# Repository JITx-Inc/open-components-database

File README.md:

# Open Component Database
 
This is an open database of components and circuit generators for automated circuit board design. Think of it as a software library for electrical engineering. We welcome contributions of component models, as well as parametric circuit generators. If you contribute to this library your expert hardware engineering knowledge becomes reusable and sharable, having the same impact as open-source software.

Components are modeled with the standardized open-source Electronic Systems Intermediate Representation (ESIR) developed by JITX for the national Electronic Resurgence Initiative.

# Organization
| File/Folder   | Description |
| ------------- |-------------|
| `artwork/`      | Examples demonstrating how to add artwork to the design. |
| `components/`      | Component data for electrical components, including circuits specific to a component. |
| `components/<manufacturer>`   | Components are organized into folders based on manufacturer |
| `components/manufacturer/<MPN>.stanza`   | There is one file per component family in the manufacturer folder (e.g. `analog-devices/ADM7150.stanza` models the ADM7150 LDOs). This file contains component data, and component-specific package models and modules.|
| `derating/`      | Contains collections of derating parameters for reliability testing. |
| `derating/space-derating.stanza`      | Derating parameters for spaceflight applications. |
| `designs/`      | Collection of example designs. [More documentation here.](designs/example-designs.md) |
| `doc/`      | Documentation. |
| `manufacturers/`      | Directory of PCB fabrication and manufacturing data like rules and stack-up definitions.|
| `modules/`      | Contains generators for subcircuits. (e.g. passive-circuits.stanza contains generators for circuits like passive filters and voltage dividers) |
| `modules/solvers`      | Contains JITX circuit solvers. (e.g. voltage-divider.stanza contains a solver for creating a resistive voltage divider taking into account component tolerance and availability) |
| `utils/`      | Utilities for modeling components and creating circuit generators|
| `utils/bundles.stanza`      | Definitions for commonly used bundles (e.g. `SPI`) |
| `utils/checks.stanza`      | Checks to run on designs (e.g. `check resistor()`|
| `utils/connects.stanza`      | Connection statements for creating io-translation/conditioning circuitry. (e.g. `isolate()`|
| `utils/generator-utils.stanza`      | General purpose utilities for modeling components and creating circuit generators. |
| `utils/generic-components.stanza`      | Collection of generic components (e.g. generic resistors, or banana-plugs)|
| `utils/landpatterns.stanza`      | Generators for land-pattern geometry (e.g. `make-qfn-landpattern()`)|
| `utils/property-structs.stanza`      | Pre-defined properties that can be applied to components, nets, modules in a design which are helpful to enable checks on the design. |
| `utils/symbols.stanza`      | Pre-defined schematic symbols (e.g. `power symbols, resistors, capacitors, diodes, etc`)|
| `utils/tolerance.stanza`      | Description of `Toleranced()` data-type and associated support functions. |

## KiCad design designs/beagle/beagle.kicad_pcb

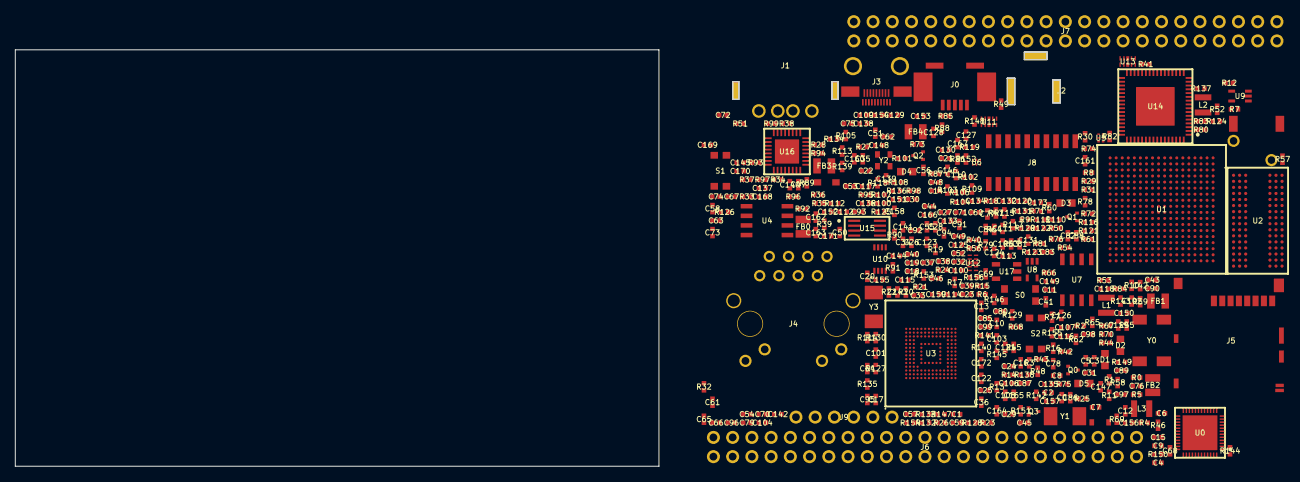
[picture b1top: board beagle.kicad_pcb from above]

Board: 4 copper layers, 383 parts (0 on the bottom side), 308 nets, no tracks yet.

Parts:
C0, C1, C2, C3, C4, C5, C6, C7, C8, C9, C10, C11, C12, C13, C14, C15, C16, C17, C18, C19, C20, C21, C22, C23, C24, C25, C26, C27, C28, C29, C30, C31, C32, C33, C34, C35, C36, C37, C38, C39, C40, C41, C42, C43, C44, C45, C46, C47, C48, C49, C50, C51, C52, C53, C54, C55, C56, C57, C58, C59, C60, C61, C62, C63, C64, C65, C66, C67, C68, C69, C70, C71, C72, C73, C74, C75, C76, C77, C78, C79, C80, C81, C82, C83, C84, C85, C86, C87, C88, C89, C90, C91, C92, C93, C94, C95, C96, C97, C98, C99, C100, C101, C102, C103, C104, C105, C106, C107, C108, C109, C110, C111, C112, C113, C114, C115, C116, C117, C118, C119, C120, C121, C122, C123, C124, C125, C126, C127, C128, C129, C130, C131, C132, C133, C134, C135, C136, C137, C138, C139, C140, C141, C142, C143, C144, C145, C146, C147, C148, C149, C150, C151, C152, C153, C154, C155, C156, C157, C158, C159, C160, C161, C162, C163, C164, C165, C166, C167, C168, C169, C170, C171, C172, C173: ipc-two-pin-package$83
D1, D2, D3, D4, D5: ipc-two-pin-package$360
FB0, FB1, FB2, FB3, FB4: ipc-two-pin-package$214
J0: usb_5Ffootprint
J1: usb-87520-0010BLF-package
J2: footprint$55
J3: hdmi-10118241-001RLF-package
J4: eth_5Ffootprint
J5: usd-2201778-1-package
J6, J7: p46_5Ffootprint
J8: RSM-110-02-S-D_5Ffootprint
J9: _5F68000-406HLF_5Ffootprint
L1, L2, L3: ind_5Ffootprint
Q0, Q1, Q2, Q3: SOT-523
R0, R1, R2, R3, R4, R5, R6, R7, R8, R9, R10, R11, R12, R13, R14, R15, R16, R17, R18, R19, R20, R21, R22, R23, R24, R25, R26, R27, R28, R29, R30, R31, R32, R33, R34, R35, R36, R37, R38, R39, R40, R41, R42, R43, R44, R45, R46, R47, R48, R49, R50, R51, R52, R53, R54, R55, R56, R57, R58, R59, R60, R61, R62, R63, R64, R65, R66, R67, R68, R69, R70, R71, R72, R73, R74, R75, R76, R77, R78, R79, R80, R81, R82, R83, R84, R85, R86, R87, R88, R89, R90, R91, R92, R93, R94, R95, R96, R97, R98, R99, R100, R101, R102, R103, R104, R105, R106, R107, R108, R109, R110, R111, R112, R113, R114, R115, R116, R117, R118, R119, R120, R121, R122, R123, R124, R125, R126, R127, R128, R129, R130, R131, R132, R133, R134, R135, R136, R137, R138, R139, R140, R141, R142, R143, R144, R145, R146, R147, R148, R149, R150, R151, R152, R153, R154, R155, R156: ipc-two-pin-package$83
S0, S1, S2: footprint$17
U0: qfn-package$76
U1: bga-pkg$130
U2: bga-pkg$301
U3: bga-pkg$326
U4: footprint$12
U5, U6: uson-dry0006a
U7: footprint$42
U8, U9: dck-R-PDSO-G5
U10: dcu-S-PDSO-G8
U11, U12: footprint$61
U13: footprint$67
U14: QFN64_5FWITHTHERMALPAD
U15: sm8-package$425
U16: QFN32_5FWITHTHERMALPAD
U17: SOT-23-5-package
Y0: xtal_5Ffootprint
Y1, Y3: SMD-2$370
Y2: SDMB-24-576MHZ-package

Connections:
AIN0: J7.39, U1.B6
AIN1: J7.40, U1.C7
AIN2: J7.37, U1.B7
AIN3: J7.38, U1.A7
AIN4: J7.33, U1.C8
AIN5: J7.36, U1.B8
AIN6: J7.35, U1.A8
AIN7: R77.2, R78.2, U1.C9
B_UART0_RX: J9.4, R114.2, U10.2
B_UART0_TX: J9.5, U10.3
CLKOUT2: J7.41, J8.18, R120.2, R121.2
CLKOUT_SRC: R120.1, U1.D14
CPU_vdd_pll: C47.1, C48.1, C49.1, C50.1, FB0.2, U1.E7, U1.H15, U1.R10, U1.R11
DDR3L_ZQ: R12.1, U2.L8
DDR_A0: U1.F3, U2.N3
DDR_A1: U1.H1, U2.P7
DDR_A2: U1.E4, U2.P3
DDR_A3: U1.C3, U2.N2
DDR_A4: U1.C2, U2.P8
DDR_A5: U1.B1, U2.P2
DDR_A6: U1.D5, U2.R8
DDR_A7: U1.E2, U2.R2
DDR_A8: U1.D4, U2.T8
DDR_A9: U1.C1, U2.R3
DDR_A10: U1.F4, U2.L7
DDR_A11: U1.F2, U2.R7
DDR_A12: U1.E3, U2.N7
DDR_A13: U1.H3, U2.T3
DDR_A14: U1.H4, U2.T7
DDR_BA0: U1.C4, U2.M2
DDR_BA1: U1.E1, U2.N8
DDR_BA2: U1.B3, U2.M3
DDR_CASn: U1.F1, U2.K3
DDR_CKE: R7.1, U1.G3, U2.K9
DDR_CLK: U1.D2, U2.J7
DDR_CLKn: U1.D1, U2.K7
DDR_CSn: U1.H2, U2.L2
DDR_D0: U1.M3, U2.E3
DDR_D1: U1.M4, U2.F7
DDR_D2: U1.N1, U2.F2
DDR_D3: U1.N2, U2.F8
DDR_D4: U1.N3, U2.H3
DDR_D5: U1.N4, U2.H8
DDR_D6: U1.P3, U2.G2
DDR_D7: U1.P4, U2.H7
DDR_D8: U1.J1, U2.D7
DDR_D9: U1.K1, U2.C3
DDR_D10: U1.K2, U2.C8
DDR_D11: U1.K3, U2.C2
DDR_D12: U1.K4, U2.A7
DDR_D13: U1.L3, U2.A2
DDR_D14: U1.L4, U2.B8
DDR_D15: U1.M1, U2.A3
DDR_DQM0: U1.M2, U2.E7
DDR_DQM1: U1.J2, U2.D3
DDR_DQS0: U1.P1, U2.F3
DDR_DQS1: U1.L1, U2.C7
DDR_DQSN0: U1.P2, U2.G3
DDR_DQSN1: U1.L2, U2.B7
DDR_ODT: U1.G1, U2.K1
DDR_RASn: U1.G4, U2.J3
DDR_RESETn: R6.1, U1.G2, U2.T2
DDR_VREF: C60.1, C107.1, C108.1, R13.2, R14.1, U1.J4, U2.H1, U2.M8
DDR_WEn: U1.B2, U2.L3
DGND: C0.2, C1.2, C2.2, C3.2, C4.2, C5.2, C6.2, C7.2, C8.2, C9.2, C10.2, C11.2, C12.2, C13.2, C14.2, C15.2, C16.2, C17.2, C18.2, C19.2, C20.2, C21.2, C22.2, C23.2, C24.2, C25.2, C26.2, C27.2, C28.2, C29.2, C30.2, C31.2, C32.2, C33.2, C34.2, C35.2, C36.2, C37.2, C38.2, C39.2, C40.2, C41.2, C42.2, C43.2, C44.2, C45.2, C46.2, C47.2, C48.2, C49.2, C50.2, C51.2, C52.2, C53.2, C54.2, C55.2, C56.2, C57.2, C58.2, C59.2, C60.2, C61.2, C62.2, C63.2, C64.2, C65.2, C66.2, C67.2, C68.2, C69.2, C70.2, C71.2, C72.2, C73.2, C74.2, C75.2, C76.2, C77.2, C78.2, C79.2, C80.2, C81.2, C82.2, C83.2, C84.2, C89.2, C90.2, C91.2, C92.2, C93.2, C94.2, C95.2, C96.2, C97.2, C98.2, C99.2, C100.2, C101.2, C102.2, C103.2, C104.2, C105.2, C106.2, C107.2, C108.2, C109.2, C110.2, C111.2, C112.2, C113.2, C114.2, C115.2, C116.2, C117.2, C122.2, C123.2, C125.2, C126.2, C127.2, C128.2, C129.2, C130.2, C131.2, C132.2, C133.2, C134.2, C135.2, C136.2, C137.2, C138.2, C139.2, C140.2, C141.2, C142.2, C145.2, C146.2, C147.2, C148.2, C149.2, C152.2, C153.2, C154.2, C155.2, C156.2, C157.2, C158.2, C159.2, C160.2, C161.2, C162.2, C163.2, C164.2, C165.2, C166.2, C167.2, C168.2, C169.2, C170.2, C171.2, C172.1, C173.1, FB2.1, J0.5, J1.4, J2.2, J2.3, J3.4, J3.7, J3.10, J3.13, J3.16, J4.8, J5.6, J5.10, J6.1, J6.2, J7.1, J7.2, J7.43, J7.44, J7.45, J7.46, J8.4, J8.8, J8.10, J8.12, J8.16, J8.20, J9.1, Q0.3, Q1.3, Q2.3, Q3.3, R4.2, R5.2, R7.2, R8.2, R10.2, R12.2, R14.2, R28.2, R30.2, R31.2, R32.2, R33.2, R34.2, R39.2, R41.2, R44.2, R53.2, R55.2, R65.2, R70.2, R72.2, R74.2, R76.2, R78.1, R92.2, R93.2, R94.2, R95.2, R99.2, R114.1, R116.1, R124.2, R126.2, R128.2, R130.2, R132.2, R134.2, R136.2, R138.2, R140.2, R142.2, R144.2, R146.2, R148.2, R150.2, R152.2, R154.2, S0.2, S0.4, S1.2, S1.4, S2.2, S2.4, U0.30, U0.41, U0.49, U1.A1, U1.A18, U1.F8, U1.G8, U1.G9, U1.G11, U1.G12, U1.H6, U1.H7, U1.H8, U1.H9, U1.H10, U1.H12, U1.J6, U1.J7, U1.J8, U1.J9, U1.J10, U1.J11, U1.K7, U1.K9, U1.K10, U1.K11, U1.L10, U1.L11, U1.L12, U1.L13, U1.M6, U1.M7, U1.M8, U1.M9, U1.M10, U1.M12, U1.M14, U1.N7, U1.N10, U1.N11, U1.N14, U1.V1, U1.V18, U2.A9, U2.B1, U2.B3, U2.B9, U2.D1, U2.D8, U2.E1, U2.E2, U2.E8, U2.F9, U2.G1, U2.G8, U2.G9, U2.J2, U2.J8, U2.M1, U2.M9, U2.P1, U2.P9, U2.T1, U2.T9, U3.A6, U3.C4, U3.E7, U3.G5, U3.H10, U3.J5, U3.K8, U3.N2, U3.N5, U3.P4, U3.P6, U4.5, U4.6, U4.7, U4.8, U5.4, U6.4, U7.1, U9.3, U10.1, U10.4, U11.3, U11.8, U12.3, U12.8, U13.3, U13.8, U14.8, U14.9, U14.16, U14.17, U14.18, U14.19, U14.53, U14.54, U14.61, U14.62, U14.63, U14.65, U15.4, U16.33, U17.2, Y2.2
DVI_+5V: J3.19, R85.2, R86.2
EARTH_GND: J0.6, J0.7, J0.8, J0.9, J1.5, J1.6, J3.20, J3.21, J3.22, J3.23, J4.15, J4.16, J5.11, J5.12, J5.13, J5.14, J5.15, J5.16, R41.1
EHRPWM1A: J7.14, U1.U14
EHRPWM1B: J7.16, U1.T14
EHRPWM2A: J6.19, U1.U10
EHRPWM2B: J6.13, U1.T10
ETH_TXD4: R99.1, U16.18
FF_Q: R88.1, U15.5
GNDA_ADC: C85.2, C86.2, C87.2, C88.2, FB2.2, J7.34, U1.A9, U1.E8
GND_OSC0: C120.2, C121.2, R65.1, R68.2, U1.V11
GND_OSC1: C118.2, C119.2, R68.1, U1.A5
GPIO0_7: J7.42, R122.2, R123.2
GPIO0_7SRC: R122.1, U1.C18
GPIO0_26: J6.14, U1.T11
GPIO0_27: J6.17, U1.U12
GPIO1_12: J6.12, U1.T12
GPIO1_13: J6.11, U1.R12
GPIO1_14: J6.16, U1.V13
GPIO1_15: J6.15, U1.U13
GPIO1_16: J7.15, R118.2, R119.2
GPIO1_17: J7.23, U1.V14
GPIO1_28: J7.12, U1.U18
GPIO1_29: J6.26, U1.V6
GPIO2_1: J6.18, U1.V12
GPIO3_18: R123.1, U1.B12
GPIO3_19: J7.27, U1.C13
GPIO3_20: R121.1, U1.D13
GPIO3_21: J7.25, R87.2, U1.A14
GRNA: J4.9, U16.3
HDMI_12MHZ: R88.2, U14.27
HDMI_CEC: J3.15, U13.4, U14.30
HDMI_DSCL: J3.17, R85.1, U13.1, U14.33
HDMI_DSDA: J3.18, R86.1, U13.2, U14.32
HDMI_HPD: J3.1, U13.5, U14.31
HDMI_INT: R84.1, U1.U16, U14.50
HDMI_TX0_N: J3.11, U12.1, U14.39
HDMI_TX0_P: J3.9, U12.2, U14.40
HDMI_TX1_N: J3.8, U11.4, U14.42
HDMI_TX1_P: J3.6, U11.5, U14.43
HDMI_TX2_N: J3.5, U11.1, U14.44
HDMI_TX2_P: J3.3, U11.2, U14.45
HDMI_TXC_N: J3.14, U12.4, U14.37
HDMI_TXC_P: J3.12, U12.5, U14.38
I2C0_SCL: R2.1, R45.1, U0.28, U1.C16, U14.52, U17.1
I2C0_SDA: R3.1, R46.1, U0.27, U1.C17, U14.51, U17.3
I2C1_SCL: J7.17, R47.1, U1.B16
I2C1_SDA: J7.18, R48.1, U1.A16
I2C2_SCL: J7.19, R49.1, U1.D18
I2C2_SDA: J7.20, R50.1, U1.D17
JTAG_EMU0: J8.13, R115.2, R117.2, U1.C14
JTAG_EMU1: J8.14, U1.B14
JTAG_TCK: J8.9, J8.11, U1.A12
JTAG_TDI: J8.3, U1.B11
JTAG_TDO: J8.7, U1.A11
JTAG_TMS: J8.1, U1.C11
JTAG_TRSTn: J8.2, R116.2, U1.B10
LCDDE: R82.2, U1.R6
LCDHSYNC: R81.2, U1.R5
LCDPCLK: R83.2, U1.V5
LCDVSYNC: R80.2, U1.U5
LCD_DATA0: C152.1, J6.45, R134.1, R135.1, U1.R1, U14.15
LCD_DATA1: C153.1, J6.46, R136.1, R137.1, U1.R2, U14.13
LCD_DATA2: C154.1, J6.43, R124.1, R125.1, R156.1, U1.R3, U14.12
LCD_DATA3: C155.1, J6.44, R126.1, R127.1, U1.R4, U14.11
LCD_DATA4: C156.1, J6.41, R128.1, R129.1, U1.T1, U14.10
LCD_DATA5: C157.1, J6.42, R130.1, R131.1, U1.T2, U14.7
LCD_DATA6: C158.1, J6.39, R138.1, R139.1, U1.T3, U14.6
LCD_DATA7: C159.1, J6.40, R140.1, R141.1, U1.T4, U14.3
LCD_DATA8: C160.1, J6.37, R142.1, R143.1, U1.U1, U14.2
LCD_DATA9: C161.1, J6.38, R144.1, R145.1, U1.U2, U14.1
LCD_DATA10: C162.1, J6.36, R146.1, R147.1, U1.U3, U14.64
LCD_DATA11: C163.1, J6.34, R148.1, R149.1, U1.U4, U14.60
LCD_DATA12: C164.1, J6.35, R150.1, R151.1, U1.V2, U14.59
LCD_DATA13: C165.1, J6.33, R152.1, R153.1, U1.V3, U14.58
LCD_DATA14: C166.1, J6.31, R132.1, R133.1, U1.V4, U14.57
LCD_DATA15: C167.1, J6.32, R154.1, R155.1, U1.T5, U14.56
LCD_DE: J6.30, R82.1, U14.20
LCD_HSYNC: J6.29, R81.1, U14.22
LCD_PCLK: J6.28, R83.1, U14.4
LCD_VSYNC: J6.27, R80.1, U14.21
LDO_PGOOD: U0.46, U1.B5
LEDAA: D2.1, R69.2
LEDAC: D2.2, Q0.1
LEDBA: D3.1, R71.2
LEDBC: D3.2, Q1.1
LEDCA: D4.1, R73.2
LEDCC: D4.2, Q2.1
LEDDA: D5.1, R75.2
LEDDC: D5.2, Q3.1
LOOP_12M: U15.2, U15.3
MDIO_CLK: U1.M18, U16.17
MDIO_DATA: U1.M17, U16.16
MII1_COL: R109.1, U1.H16
MII1_CRS_DV: R110.1, U1.H17
MII1_REFCLK: R111.2, R112.1, R113.1
MII1_RXCLK: R106.1, U1.L18
MII1_RXD0: R104.1, U1.M16
MII1_RXD1: R103.1, U1.L15
MII1_RXD2: R102.1, U1.L16
MII1_RXD3: R101.1, U1.L17
MII1_RXDV: R105.1, U1.J17
MII1_RXERR: R107.1, U1.J15
MII1_TXCLK: R108.1, U1.K18
MMC0_CD: J5.9, J8.19, R56.2, U1.C15
MMC0_CLKO: J5.5, R62.2, U1.G17
MMC0_CMD: J5.3, R61.2, U1.G18
MMC0_DAT0: J5.7, R57.2, U1.G16
MMC0_DAT1: J5.8, R58.2, U1.G15
MMC0_DAT2: J5.1, R59.2, U1.F18
MMC0_DAT3: J5.2, R60.2, U1.F17
MMC1_CLK: J6.21, R25.2, U1.U9, U3.M6
MMC1_CMD: J6.20, R16.2, U1.V9, U3.M5
MMC1_DAT0: J6.25, R17.2, U1.U7, U3.A3
MMC1_DAT1: J6.24, R18.2, U1.V7, U3.A4
MMC1_DAT2: J6.5, R19.2, U1.R8, U3.A5
MMC1_DAT3: J6.6, R20.2, U1.T8, U3.B2
MMC1_DAT4: J6.23, R21.2, U1.U8, U3.B3
MMC1_DAT5: J6.22, R22.2, U1.V8, U3.B4
MMC1_DAT6: J6.3, R23.2, U1.R9, U3.B5
MMC1_DAT7: J6.4, R24.2, U1.T9, U3.B6
MODE2: R96.1, R109.2, U16.15
OSC0_IN: C120.1, R64.1, U1.V10, Y1.1
OSC0_OUT: R63.2, R64.2, U1.U11
OSC1_IN: C118.1, R67.1, U1.A6, Y0.1
OSC1_OUT: R66.2, R67.2, U1.A4
PHYX: C144.1, R90.1, Y3.2
PHY_XTAL1: C143.1, R91.1, Y3.1
PHY_XTAL2: R90.2, R91.2, U16.4
PMIC_INT: R1.1, U0.45, U1.B18
PMIC_ISET1: R4.1, U0.35
PMIC_ISET2: R5.1, U0.36
PMIC_PGOOD: U0.26, U1.B15, U1.R14, U9.2
PMIC_POWR_EN: U0.9, U1.C6
PMIC_VOUT_VDCDC1: C9.1, L1.2, U0.19
PMIC_VOUT_VDCDC2: C11.1, L2.2, U0.24
PMIC_VOUT_VDCDC3: C13.1, L3.2, U0.29
PMIC_bypass: C5.1, U0.47
PMIC_int_ldo: C4.1, U0.48
PMIC_sw1: L1.1, U0.20
PMIC_sw2: L2.1, U0.23
PMIC_sw3: L3.1, U0.31
PWR_BUT: J7.9, S0.1, S0.3, U0.25
PWR_LEDR: D1.2, R44.1
RCLKIN: R113.2, U16.5
REFCLK0: R92.1, R106.2, R112.2, U16.7
RXD0_MODE0: R98.1, R104.2, U16.11
RXD1_MODE1: R97.1, R103.2, U16.10
RXN: C171.1, J4.6, R38.1, U16.30
RXP: C170.1, J4.3, R37.1, U16.31
SDBOOT: R156.2, S2.1, S2.3
SPI1_CS0: J7.28, U1.C12, U14.25
SPI1_D0: J7.29, U1.B13, U14.24
SPI1_D1: J7.30, U1.D12
SPI1_SCLK: J7.31, U1.A13, U14.23
SYS_5V: C2.1, C8.1, C10.1, C12.1, C14.1, C17.1, C19.1, C115.1, C122.1, J7.7, J7.8, R69.1, R71.1, R73.1, R75.1, U0.2, U0.7, U0.8, U0.21, U0.22, U0.32, U0.39, U0.42, U4.2, U7.2, U7.3
SYS_RESETn: C146.1, C173.2, J7.10, J8.15, R51.1, R79.2, S1.1, S1.3, U1.A10, U9.4, U16.19
TCT_RCT: C136.1, J4.4, J4.5, R100.1
TIMER4: J6.7, U1.R7
TIMER5: J6.9, U1.T6
TIMER6: J6.10, U1.U6
TIMER7: J6.8, U1.T7
TXN: C169.1, J4.2, R36.1, U16.28
TXP: C168.1, J4.1, R35.1, U16.29
U5_H18: R111.1, U1.H18
U5_R13: R119.1, U1.R13
U5_T13: R118.1, U1.T13
UART0_RX: U1.E15, U10.6
UART0_TX: U1.E16, U10.5
UART1_RXD: J7.26, U1.D16
UART1_TXD: J7.24, U1.D15
UART2_RXD: J7.22, U1.A17
UART2_TXD: J7.21, U1.B17
UART4_RXD: J7.11, U1.T17
UART4_TXD: J7.13, U1.U17
USB0_DM: J0.2, U1.N18, U5.2
USB0_DP: J0.3, U1.N17, U5.1
USB0_ID: J0.4, U1.P16, U5.3
USB1_DM: J1.2, U1.R18, U6.2
USB1_DP: J1.3, U1.R17, U6.1
USB1_DRVVBUS: R55.1, U1.F15, U7.4
USB1_ID: R53.1, U1.P17
USB1_OCn: R29.1, U1.T16, U7.5
USB1_PWR: C123.1, C148.1, C149.1, FB3.1, R54.2, U6.6, U7.6, U7.7, U7.8
USB1_VBUS: R54.1, U1.T18
USB_DC: C1.1, C147.1, J0.1, R52.1, U0.12, U5.6
USR0: Q0.2, R70.1, U1.V15
USR1: Q1.2, R72.1, U1.U15
USR2: Q2.2, R74.1, U1.T15
USR3: Q3.2, R76.1, U1.V16
VBUS: C137.1, C138.1, C139.1, FB3.2, J1.1, R35.2, R36.2, R37.2, R38.2, R100.2, U16.1, U16.27
VDDS: C80.1, C81.1, C82.1, C83.1, C84.1, R42.2, U1.E6, U1.E14, U1.F9, U1.K13, U1.N6, U1.P9, U1.P14
VDDS_DDR: C52.1, C53.1, C54.1, C55.1, C56.1, C57.1, C58.1, C59.1, C91.1, C92.1, C93.1, C94.1, C95.1, C96.1, C97.1, C98.1, C99.1, C100.1, C101.1, C102.1, C103.1, C104.1, C105.1, C106.1, R6.2, R13.1, U1.E5, U1.F5, U1.G5, U1.H5, U1.J5, U1.K5, U1.L5, U2.A1, U2.A8, U2.B2, U2.C1, U2.C9, U2.D2, U2.D9, U2.E9, U2.F1, U2.G7, U2.H2, U2.H9, U2.K2, U2.K8, U2.N1, U2.N9, U2.R1, U2.R9
VDD_1V8: C18.1, C44.1, C45.1, C46.1, FB0.1, FB1.1, U0.40, U1.D10, U1.E9, U1.N16, U1.R16
VDD_3V3A: C20.1, C51.1, C61.1, C62.1, C63.1, C64.1, C65.1, C66.1, C67.1, C68.1, C69.1, C70.1, C71.1, C72.1, C73.1, C74.1, C75.1, C76.1, C77.1, C78.1, C79.1, C125.1, C135.1, C145.1, R0.2, R1.2, R2.2, R3.2, R29.2, R40.1, R42.1, R43.1, R45.2, R46.2, R47.2, R48.2, R49.2, R50.2, R51.2, R125.2, R127.2, R129.2, R131.2, R133.2, R135.2, R137.2, R139.2, R141.2, R143.2, R145.2, R147.2, R149.2, R151.2, R153.2, R155.2, U0.18, U0.43, U1.E10, U1.E11, U1.E12, U1.E13, U1.F14, U1.G14, U1.H14, U1.J14, U1.K14, U1.L14, U1.N5, U1.N15, U1.P5, U1.P6, U1.P7, U1.P8, U1.P10, U1.P11, U1.P12, U1.P13, U1.R15, U4.1, U9.5, U15.6, U15.7, U15.8, U17.4, Y2.4
VDD_3V3AUX: C16.1, D1.1, U0.1
VDD_3V3B: C109.1, C110.1, C111.1, C112.1, C116.1, C126.1, C142.1, C150.1, C150.2, C151.1, C151.2, C172.2, FB4.1, J5.4, J7.3, J7.4, J8.5, R15.1, R16.1, R17.1, R18.1, R19.1, R20.1, R21.1, R22.1, R23.1, R24.1, R27.1, R56.1, R57.1, R58.1, R59.1, R60.1, R61.1, R62.1, R77.1, R84.2, R89.1, R96.2, R97.2, R98.2, R115.1, R117.1, U3.C6, U3.E6, U3.F5, U3.J10, U3.K9, U3.M4, U3.N4, U3.P3, U3.P5, U4.3, U10.7, U10.8, U16.12
VDD_5V: C0.1, J2.1, J7.5, J7.6, U0.10
VDD_ADC: C85.1, FB1.2, J7.32, R9.1, U1.D8
VDD_CORE: C21.1, C22.1, C23.1, C24.1, C25.1, C26.1, C27.1, C28.1, C29.1, C30.1, C31.1, C32.1, C33.1, C34.1, C35.1, C36.1, U1.F6, U1.F7, U1.G6, U1.G7, U1.G10, U1.H11, U1.J12, U1.K6, U1.K8, U1.K12, U1.L6, U1.L7, U1.L8, U1.L9, U1.M11, U1.M13, U1.N8, U1.N9, U1.N12, U1.N13
VDD_MPU: C37.1, C38.1, C39.1, C40.1, U1.F10, U1.F11, U1.F12, U1.F13, U1.G13, U1.H13, U1.J13
VRTC: C89.1, R11.2, R43.2, U1.D7
WAKEUP: R0.1, R11.1, U0.13, U1.C5
XDMA_EVENT_INTRO: J8.17, U15.1
XTAL0_OUT: C121.1, R63.1, Y1.2
XTAL1_OUT: C119.1, R66.1, Y0.4
Y4_CLK: R87.1, Y2.3
YELA: J4.12, R39.1, U16.2
eMMC_RSTn: R15.2, R79.1, U3.K5
net_CPU_USB0_VBUS: R52.2, U1.P15
net_CPU_cpu_CAP_VBB_MPU: C43.1, U1.C10
net_CPU_cpu_CAP_VDD_RTC: C90.1, U1.D6
net_CPU_cpu_CAP_VDD_SRAM_CORE: C41.1, U1.D9
net_CPU_cpu_CAP_VDD_SRAM_MPU: C42.1, U1.D11
net_CPU_cpu_DDR_VTP: R8.1, U1.J3
net_CPU_cpu_ENZ_KALDO_1P8V: R10.1, U1.B4
net_CPU_cpu_VREFP: C86.1, C87.1, C88.1, R9.2, U1.B9
net_EEPROM_WP: R40.2, U17.5
net_ETH_CONN_GRN_C: J4.10, R33.1
net_ETH_CONN_YEL_C: J4.11, R32.1
net_ETH_TRANS_CRS: R110.2, U16.14
net_ETH_TRANS_RBIAS: R34.1, U16.32
net_ETH_TRANS_RXD2_RMIISEL: R93.1, R102.2, U16.9
net_ETH_TRANS_RXD3_PHYAD2: R94.1, R101.2, U16.8
net_ETH_TRANS_RXDV: R105.2, U16.26
net_ETH_TRANS_RXER_RXD4_PHYAD0: R95.1, R107.2, U16.13
net_ETH_TRANS_TXCLK: R108.2, U16.20
net_ETH_TRANS_VDDCR: C140.1, C141.1, U16.6
net_HDMI_TRANS_SWING: R30.1, U14.34
net_HDMI_TRANS_TEST: R31.1, U14.49
net_HDMI_TRANS_VDDA: C129.1, C130.1, U14.35, U14.36, U14.41, U14.46
net_HDMI_TRANS_VDDC: C131.1, C132.1, U14.5, U14.29
net_HDMI_TRANS_VDDIO: C133.1, C134.1, U14.14, U14.55
net_HDMI_TRANS_VDD_PLL: C127.1, C128.1, U14.47, U14.48
net_INV_BUFFER_GND: C124.2, U8.3
net_INV_BUFFER_VCC: C124.1, U8.5
net_LDO_FB: C117.1, R27.2, R28.1, U4.4
net_PMIC_BATT: C3.1, U0.4, U0.5, U0.6
net_PMIC_MUX_OUT: C6.1, U0.16
net_PMIC_VOUT_LDO1: C15.1, U0.3
net_PMIC_WLED_ANODE: C7.1, U0.38
net_Y3_OSC_GND: C143.2, C144.2
net_eMMC_eMMC_DS: R26.2, U3.H5
net_eMMC_eMMC_VDDIM: C113.1, C114.1, U3.C2

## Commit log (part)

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2023-04-20 Removed dependencies on jitx/geometry and jitx/http
2023-04-20 Removed unnecessary import esir/ir
2023-04-21 checkin for Philippe
2023-04-21 updated with schematic-groups
2023-04-22 Reduce Altium net symbol sizes by 2.54
2023-04-22 add silkscreen labels to BNC connector properly
2023-04-24 removed minimum_quantity requirement
2023-04-24 Altium gnd symbol adjustement
2023-04-24 Adjust
2023-04-25 Roll back can-stm change
2023-04-25 reformatted
2023-04-25 Updating NRF
2023-04-27 creating nrf motion design
2023-04-28 Extend nrf and antenna
2023-05-01 make USB con public
2023-05-01 fixed tolerance field
2023-05-02 updated jitx-client Dockerfile
2023-05-02 fix jlcpcb 2313 6 layer stackup
2023-05-03 updated CI docker image
2023-05-03 fixed up code to make it as runnable as possible (with separate output dirs)
2023-05-03 updated Docker image
2023-05-04 until pin assignment is fixed
2023-05-04 added one more view
2023-05-09 Add load switch modeule
2023-05-09 made more runnable designs
2023-05-10 debug on the failure of pin assignment as well as parts-db
2023-05-10 added local fail case as comment
2023-05-10 fixed mcu to a good one
2023-05-11 fixed invalid format (darn copy/paste)
2023-05-11 add optional argument for offset of add-mounting-holes
2023-05-18 JITX-5031: Map "stock" -> "min-stock"
2023-05-18 Update type signature to match more restrictive Tuple
2023-05-20 Prototype: allow setting local 3d model for Parts DB parts
2023-05-20 oops this is the latest version for the Docker image
2023-05-23 Re-add box symbol padding
2023-06-02 fixed typo
2023-06-12 JITX-5178: Add sellers data as property for component card
2023-06-16 Pin assignment ratsnest locked
2023-06-27 single component code generation
2023-06-27 Improve bypass-cap-strap
2023-06-27 too many flush :(
2023-06-27 disable comments temporarily
2023-06-28 suppoer user chosen folder
2023-06-28 show component stanza file
2023-06-28 fallback
2023-06-28 Handle missing resolved-price for resistors/capacitors
2023-06-28 Handle missing resolved-price for microcontrollers
2023-06-29 Cleaning up crystal
2023-06-29 Use optional arguments instead of overloading
2023-06-29 refactor code
2023-07-05 demo update
2023-07-05 Remove case filter from smd-inductor query, to include candidate with enough stock
2023-07-07 Fix typo in comment
2023-07-07 public more defs in ComponentCode
2023-07-08 JITX-5435: Update resonator-checks to work with Toleranced
2023-07-10 Update Toleranced() to proper usage
2023-07-14 JITX-5504: Remove "sellers" ESIR property
2023-07-19 Added a unit test for the `dnp` utility functions.
2023-07-19 Added content to make a failing and non-failing test.
    I've also added the plugin serialization logging.
2023-07-20 added optional argument to run-ocdb-tests.sh to skip expensive tests
2023-07-21 add TolerancedMinMax
2023-07-25 run-ocdb-tests.sh: change permission to be executable
2023-07-25 github workflow: Update to latest aws-actions
    to solve:
    https://github.blog/changelog/2022-10-11-github-actions-deprecating-save-state-and-set-output-commands/
    Note that "v1" and "v2" versions of aws-actions track the latest releases, so specific version
    numbers shouldn't be necessary.
2023-07-28 run-ocdb-tests.sh: don't fail on missing user.params
2023-07-28 [WIP] working on pre-amp circuit
2023-07-28 Purged the `SWD-TRACESWO` option from the SWD bundle
    Fixes JITX-5549
    This option was a duplicate of `SWD-SWO`. There are only two options
    with SWD, with or without SWO.
2023-07-28 Added power-pin properties for vio
2023-07-28 Refactored the load-switch module for more reusability
    This allows the user to pass a PMOS FET definition in
    so that this load switch's current capability can be
    parameterized.
2023-07-28 Added PWM timer bundle definitions forapplicable IO.
2023-07-28 Added new tag connect interface for Arm Cortex interface
2023-07-28 Increased the pin 1 indicator size
2023-07-28 Added temperature range specification
2023-07-28 Added a new module with functions to compute noise metrics.
2023-07-31 Added more dnp decoupling caps and no-connect indicators
2023-08-01 Add LPDDR4
2023-08-03 Updates from demo:
2023-08-03 make that public
2023-08-06 simply changed all parametric-* references to placeholder-*
2023-08-08 Move .github/jitx-client/scripts/* to scripts/* to improve usage of the test script by other repos. Fixup Dockerfile to match.
2023-08-08 scripts/run-ocdb-tests.sh: expect to start in the open-components-database directory
2023-08-08 scripts/run-ocdb-tests.sh: expect to start in the open-components-database directory (3)
2023-08-08 scripts/run-ocdb-tests.sh: expect to start in the open-components-database directory (4)
2023-08-08 changed dummy-* dev to accept package size
2023-08-08 improve variable names and removed extra fluff
2023-08-09 Updated `bypass-cap-strap` to match the `cap-strap` function.
    Previously, there was no way to pass in arbitrary parameters
    to thee `bypass-cap-strap` function. This commit now causes this function
    to have a similar signature as `cap-strap`
2023-08-10 JITX-5813: Add new 3DModel fields from parts-db
2023-08-11 Use a separate field for comment, don't include properties yet
2023-08-15 add esd
2023-08-16 scripts/run-ocdb-tests.sh: fix un-pathed jitx reference
2023-08-17 removed usage of DualOffsetVoltage()
2023-08-17 Update OCDB Altium symbols to match Altium's Power Ports
2023-08-21 CI Kick with jitx-client updated
2023-08-22 Revert "JITX-5813: Add new 3DModel fields from parts-db"
    This reverts commit 2a28eeef3d40b5fca5c86e5a7bf4e1ffd7f43613.
2023-08-23 no comments id in ESIR Model3D
2023-08-23 use times function
2023-08-24 Commit current changes
2023-08-24 Update for checks
2023-08-30 JITX-6160 fix text orientation of Altium power symbols
2023-08-30 re-order to match the order they appear in Altium GUI
2023-08-31 looks like Future will be available in 2.17
2023-09-13 added parts-db to ignore list
2023-09-20 added dnp to text & logo plus small design test
2023-09-25 target jitx-client 2.20.0
2023-09-29 [Bugfix] Fixed the multi opamp supporting symbols
    These symbols were broken - the pins were pointing backwards causing weird
    artifacts. The pin name/numbers were not configured to show correctly.
    I changed the power symbol to use horizontal VEE and VCC pins like one
    would normally do with packages like this.
2023-10-04 fixed TC2030 with correct VDD assignment
2023-10-04 Purged the SWD-TRACESWO option from the SWD bundle
    Fixes part of JITX-5549
    This option was a duplicate of `SWD-SWO`. There are only two options
    with SWD, with or without SWO.
    The TRACESWO is still used in the server backend and can't be removed
    yet until we can modify the database content.
2023-10-07 prepare OCDB for preferred component integration
2023-10-09 Remove unecessary name field
2023-10-13 remove sellers from props
2023-10-16 reroute to ocdb/utils/fonts
2023-10-17 Update for thermal pad, octal spi
2023-10-20 remove LCSC from default APPROVED-DISTRIBUTOR-LIST
2023-10-25 fixed up all voltage-divider() calls
2023-10-25 fixed Int != Double
2023-10-27 remove vendors from list. Keep only 2
2023-10-29 fixed up all refs to CustomLayer to mimic Silkscreen
2023-10-31 default bom columns for users
2023-10-31 try 2.23.1
2023-10-31 try 2.20.0
2023-10-31 try 2.24.0
2023-11-09 using a future version of jitx-client docker image
2023-11-16 Add vias to defaults
2023-11-16 Add default via
2023-11-27 updated dockerfile
2023-11-28 ref-end Int
2023-12-02 reduce number of components
2023-12-05 remove odt
2023-12-16 remove unused attributes
2023-12-19 Added SLM configuration for OCDB
    This is a trivial implementation right now because OCDB doesn't
    have any specific dependencies. This is primarily to support the
    `slm` integration into JITX.
2023-12-19 Update via
2023-12-21 Add new draft bundles
2023-12-21 Update connector for new usb-c
2023-12-21 Update connector code
2023-12-21 New usb-3 bundle
2024-01-04 changed to ocdb submodule with changes
2024-01-05 go back and use the symbols.stanza from dev
2024-01-05 go back and use the symbol-utils.stanza from dev
2024-01-05 overzealous search and replace
2024-01-05 name collision in checks
2024-01-05 sync'ed with dh/usb-bundles
2024-01-06 fixed indentation
2024-01-06 added strap() function
2024-01-07 more simplification on rated-voltage
2024-01-08 scripts/run-ocdb-tests.sh: remove version-specific python invocation
2024-01-09 scripts/evaluate_pcb_objects.py: use raw strings for regexes to properly escape backslash sequences for python 3.12
2024-01-09 fixed up checking for properties used
2024-01-10 added public tag on module/insts
2024-01-12 scripts/run-ocdb-tests.sh: allow PYTHON override
2024-01-31 Roughed out changes for HS components'
2024-02-21 Added pin-model placeholders for the database RLC parts
    This forces a pin model on the resistors and capacitors that
    get used in topologies.
2024-02-27 changed logo & text to be modules with NotInBOM
2024-02-28 fixed extra NotInBOM
2024-03-06 fixed inst defn
2024-03-06 updated version to latest
2024-03-14 Fixes for proper functioning
2024-03-14 fixed public status on mcu
2024-03-22 preparation for ODB++ importer
2024-03-28 Hash Locals instead of JITXObjects
2024-03-29 use JITX symbol for Altium power-gnd
2024-04-11 missed a few spots
2024-04-23 [Error] TopoRouter error when attempting to drop via
2024-04-29 added SPI RDY
2024-04-29 complete the reverse lookup
2024-05-06 pin to jitx-client 3.5
2024-05-08 to try and run the new docker
2024-05-09 initial for testing
2024-05-20 Split tests/all.stanza into two parts
2024-05-21 Disable stm32-mcu-props test to avoid segfault
2024-06-13 PROD-76 download model3d for res-strap etc from dbquery
2024-06-13 Bump version to 3.10.0
2024-06-13 empty commit to trigger CI
2024-06-20 Bump to 3.11.0
2024-06-24 enhance test cases to for the _exist keyword
2024-06-24 bypass JITX
2024-06-24 remove versioning
2024-06-24 try run --flags TESTING
2024-06-25 tyr 3.5
2024-06-25 remove toml file
2024-06-25 try 3.5
2024-06-25 try 3.10
2024-06-25 3.10
2024-06-26 use 3.11.1
2024-07-01 PROD-76 merge-to-dev for download-model3d
2024-07-02 need to compute landpattern before generating supports
2024-07-08 remove LFCHAO in utils/parts
2024-07-24 deduplicate various ocdb/utils packages by forwarding to legacy packages
2024-07-25 don't forward bundle names unnecessarily
2024-07-30 Bump slm.toml to 3.14.0
2024-08-01 use new keywords
2024-08-01 to 3.13.2
2024-08-01 try 3.13.1
2024-08-01 Update paper size to ISO-A4
2024-08-06 change test script
2024-08-06 fixed overdone port-to-pin conversion
2024-08-13 add import for compat. with legacy-ocdb-structures refactor
2024-08-14 replace
2024-08-15 Another place where emodels import is needed
2024-08-21 Bump slm.toml to 3.16.0
2024-08-21 accept toleranced or false
2024-08-22 Bump slm.toml to 3.15.2
2024-08-22 Bump slm.toml to 3.17.0
2024-09-03 source and non-sourcing tests
2024-09-03 try 3.16
2024-09-05 try 3.16 again
2024-09-05 add a vendor carries STM
2024-09-07 more part-query tests
2024-09-12 Bump SLM version to 3.18.0
2024-10-10 Bump version to 3.21.0
2024-12-19 Bump version to 3.24.0
2024-12-19 Bump version to 3.26.0
2025-01-15 Bump version to 3.27.0
2025-01-30 Bump version to 3.29.0
2025-02-06 Bump version to 3.30.0
2025-02-19 Bump version to 3.31.0
2025-04-03 Bump version to 3.32.0
2025-06-26 Bump version to 3.34.0
2025-07-25 Bump version to 3.35.0
2025-09-15 Bump version to 3.36.0
2025-10-31 Bump version to 4.0.0
